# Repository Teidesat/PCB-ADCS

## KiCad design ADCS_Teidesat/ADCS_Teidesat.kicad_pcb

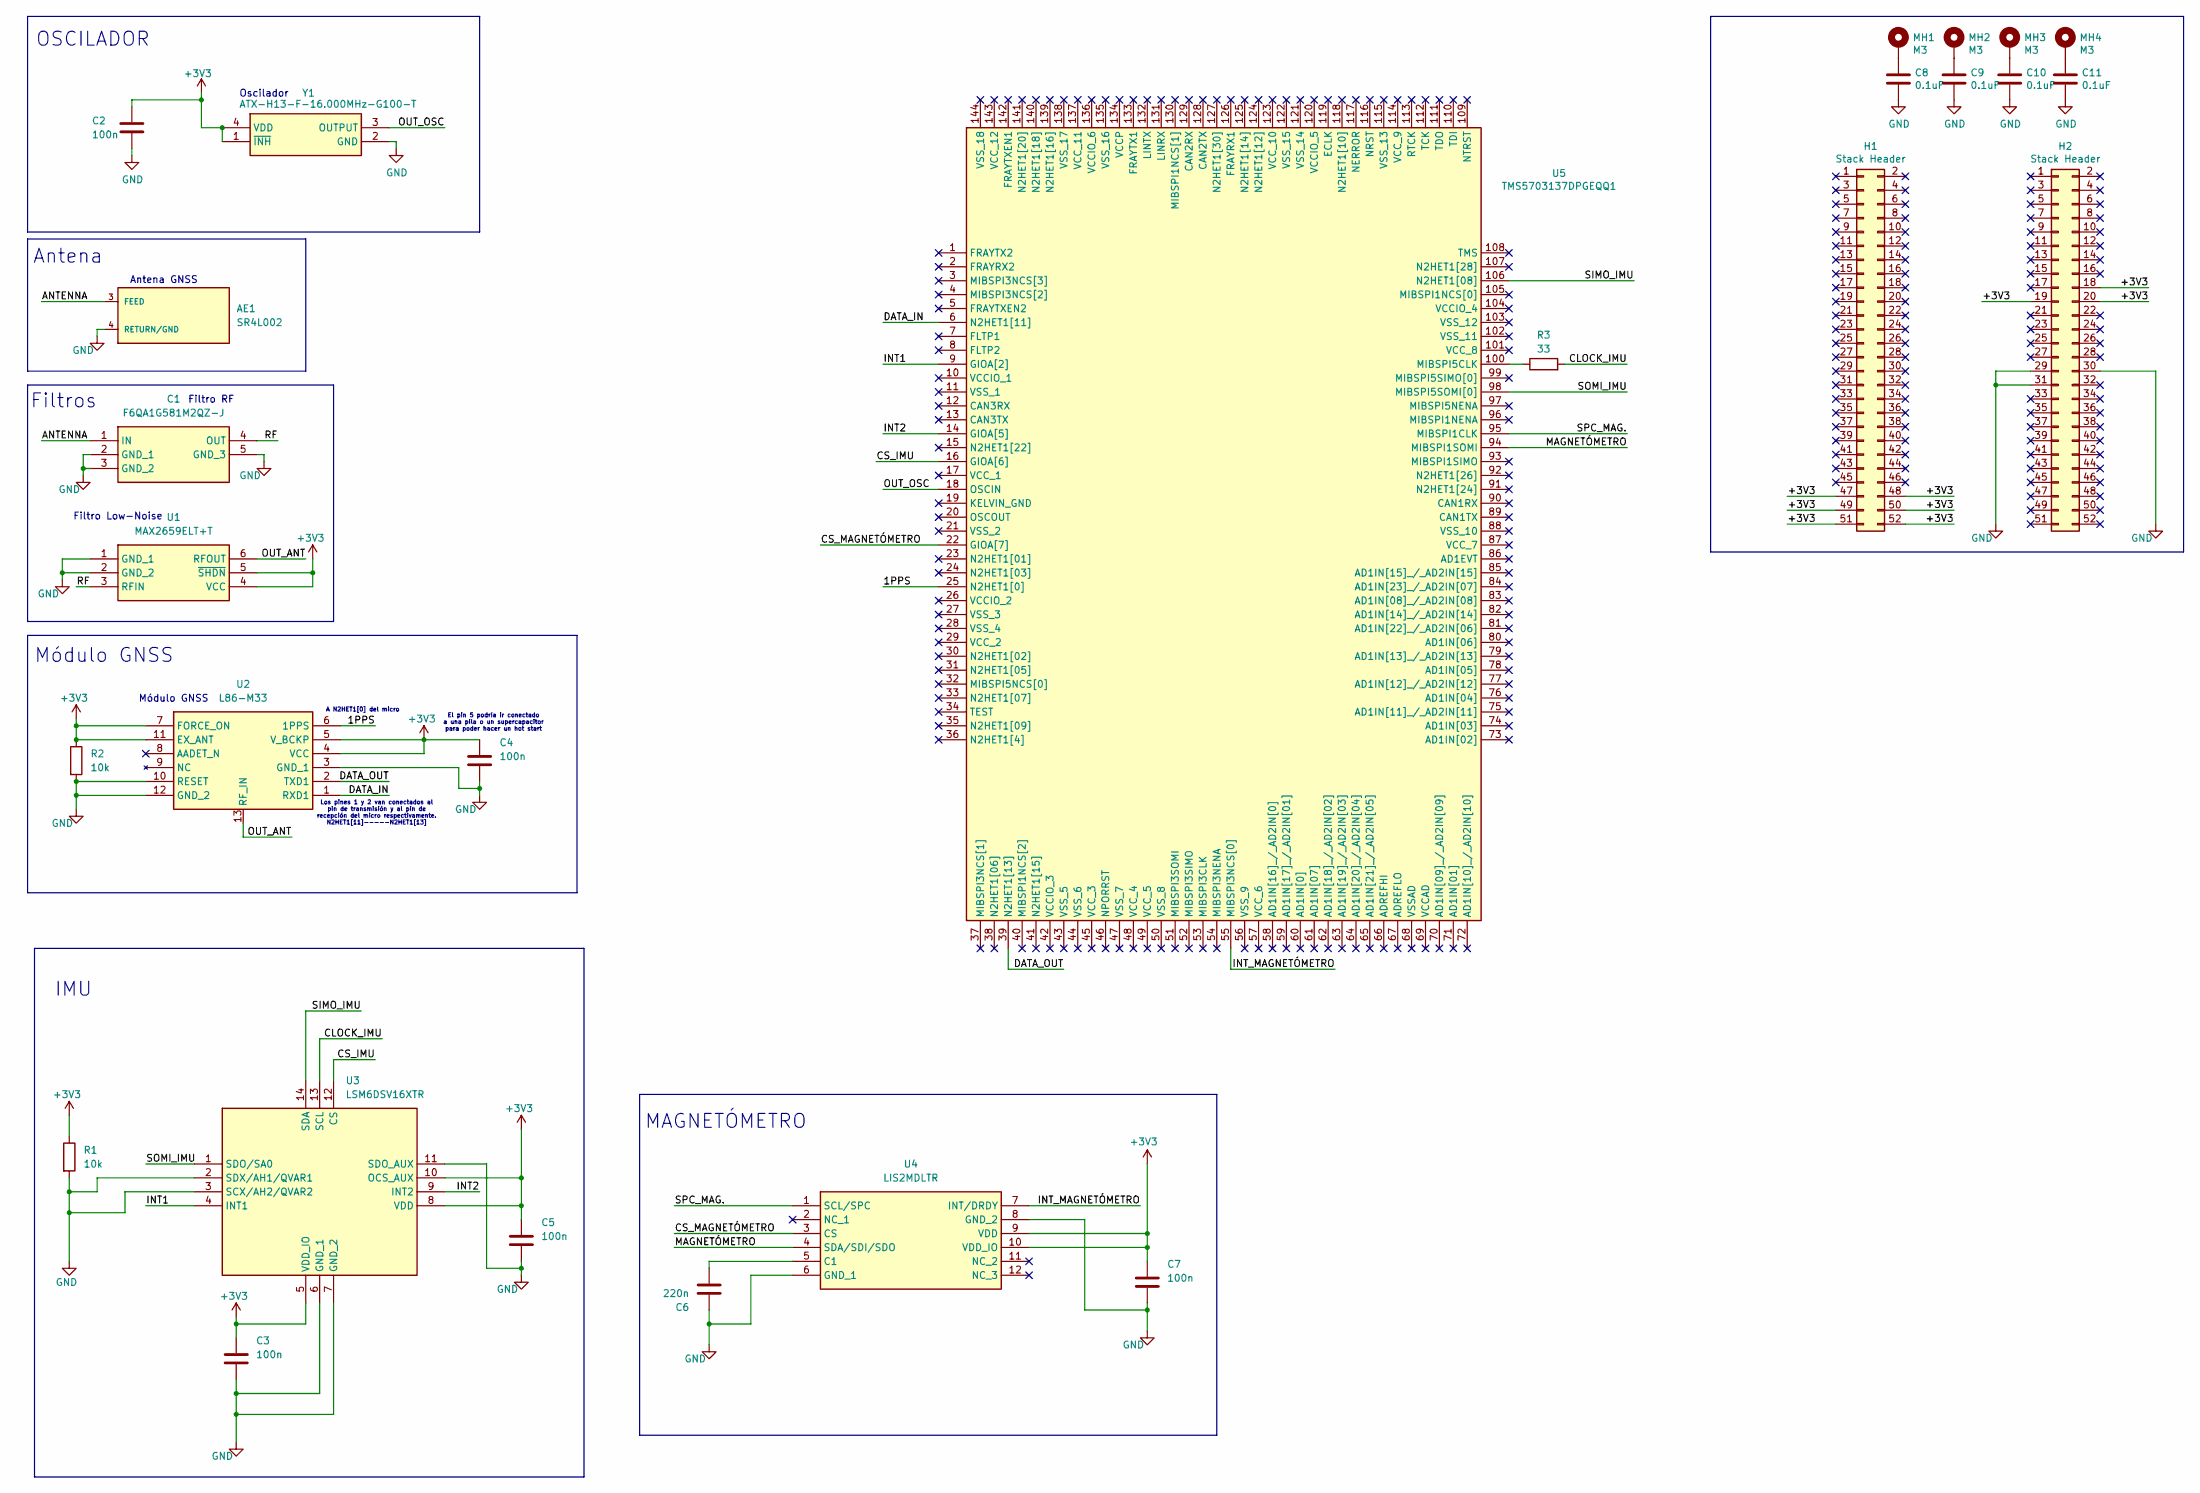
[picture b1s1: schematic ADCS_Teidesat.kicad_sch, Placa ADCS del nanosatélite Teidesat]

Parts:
AE1: SR4L002; XCVR_SR4L002
C1: F6QA1G581M2QZ-J; F6QA1G581M2QZJ; Mouser Part Number 963-F6QA1G581M2QZ-J
C2, C3, C4, C5, C7: 100n; C_0805_2012Metric
C6: 220n; C_0805_2012Metric
C8, C9, C10, C11: 0.1uF; C_0805_2012Metric
H1, H2: Stack Header; PinHeader_2x26_P2.54mm_Vertical
MH1, MH2, MH3, MH4: M3; MountingHole_3.2mm_M3_Pad
R1, R2: 10k; R_0201_0603Metric
R3: 33; R_0201_0603Metric
U1: MAX2659ELT+T; MAX2659ELTT; Mouser Part Number 700-MAX2659ELT+T
U2: L86-M33; Prueba_MODULOGNSS; Mouser Part Number 277-L86-M33
U3: LSM6DSV16XTR; XDCR_LSM6DSV16XTR; Mouser Part Number 511-LSM6DSV16XTR
U4: LIS2MDLTR; PQFN50P200X200X70-12N; Mouser Part Number 511-LIS2MDLTR
U5: TMS5703137DPGEQQ1; QFP50P2200X2200X160-144N; Manufacturer_Part_Number TMS5703137DPGEQQ1; Mouser Part Number 595-MS5703137DPGEQQ1
Y1: ATX-H13-F-16.000MHz-G100-T; ATXH13F16000MHzG100T; Mouser Part Number 815-ATXH13F1600G100T

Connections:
+3V3: C2.1, C3.1, C4.1, C5.1, C7.1, H1.47, H1.48, H1.49, H1.50, H1.51, H1.52, H2.18, H2.19, H2.20, R1.1, R2.1, U1.4 (VCC), U1.5 (~SHDN), U2.4 (VCC), U2.5 (V_BCKP), U2.7 (FORCE_ON), U2.11 (EX_ANT), U3.5 (VDD_IO), U3.8 (VDD), U3.10 (OCS_AUX), U4.9 (VDD), U4.10 (VDD_IO), Y1.1 (~INH), Y1.4 (VDD)
/1PPS: U2.6 (1PPS), U5.25 (N2HET1[0])
/ANTENNA: AE1.3 (FEED), C1.1 (IN)
/CLOCK_IMU: R3.2, U3.13 (SCL)
/CS_IMU: U3.12 (CS), U5.16 (GIOA[6])
/CS_MAGNETÓMETRO: U4.3 (CS), U5.22 (GIOA[7])
/DATA_IN: U2.1 (RXD1), U5.6 (N2HET1[11])
/DATA_OUT: U2.2 (TXD1), U5.39 (N2HET1[13])
/INT1: U3.4 (INT1), U5.9 (GIOA[2])
/INT2: U3.9 (INT2), U5.14 (GIOA[5])
/INT_MAGNETÓMETRO: U4.7 (INT/DRDY), U5.55 (MIBSPI3NCS[0])
/MAGNETÓMETRO: U4.4 (SDA/SDI/SDO), U5.94 (MIBSPI1SOMI)
/OUT_ANT: U1.6 (RFOUT), U2.13 (RF_IN)
/OUT_OSC: U5.18 (OSCIN), Y1.3 (OUTPUT)
/RF: C1.4 (OUT), U1.3 (RFIN)
/SIMO_IMU: U3.14 (SDA), U5.106 (N2HET1[08])
/SOMI_IMU: U3.1 (SDO/SA0), U5.98 (MIBSPI5SOMI[0])
/SPC_MAG.: U4.1 (SCL/SPC), U5.95 (MIBSPI1CLK)
GND: AE1.4 (RETURN/GND), C1.2 (GND_1), C1.3 (GND_2), C1.5 (GND_3), C2.2, C3.2, C4.2, C5.2, C6.1, C7.2, C8.2, C9.2, C10.2, C11.2, H2.29, H2.30, H2.31, R1.2, R2.2, U1.1 (GND_1), U1.2 (GND_2), U2.3 (GND_1), U2.10 (RESET), U2.12 (GND_2), U3.2 (SDX/AH1/QVAR1), U3.3 (SCX/AH2/QVAR2), U3.6 (GND_1), U3.7 (GND_2), U3.11 (SDO_AUX), U4.6 (GND_1), U4.8 (GND_2), Y1.2 (GND)
unnamed: C8.1, MH1.1
unnamed: C9.1, MH2.1
unnamed: C10.1, MH3.1
unnamed: C11.1, MH4.1
unnamed: C6.2, U4.5 (C1)
unnamed: R3.1, U5.100 (MIBSPI5CLK)

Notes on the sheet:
Antena GNSS
Módulo GNSS
Antena
IMU
OSCILADOR
Filtros
El pin 5 podría ir conectado a una pila o un supercapacitor para poder hacer un hot start
MAGNETÓMETRO
Filtro Low-Noise
Oscilador
A N2HET1[0] del micro
Módulo GNSS
Filtro RF
Los pines 1 y 2 van conectados al pin de transmisión y al pin de recepción del micro respectivamente. N2HET1[11]-----N2HET1[13]

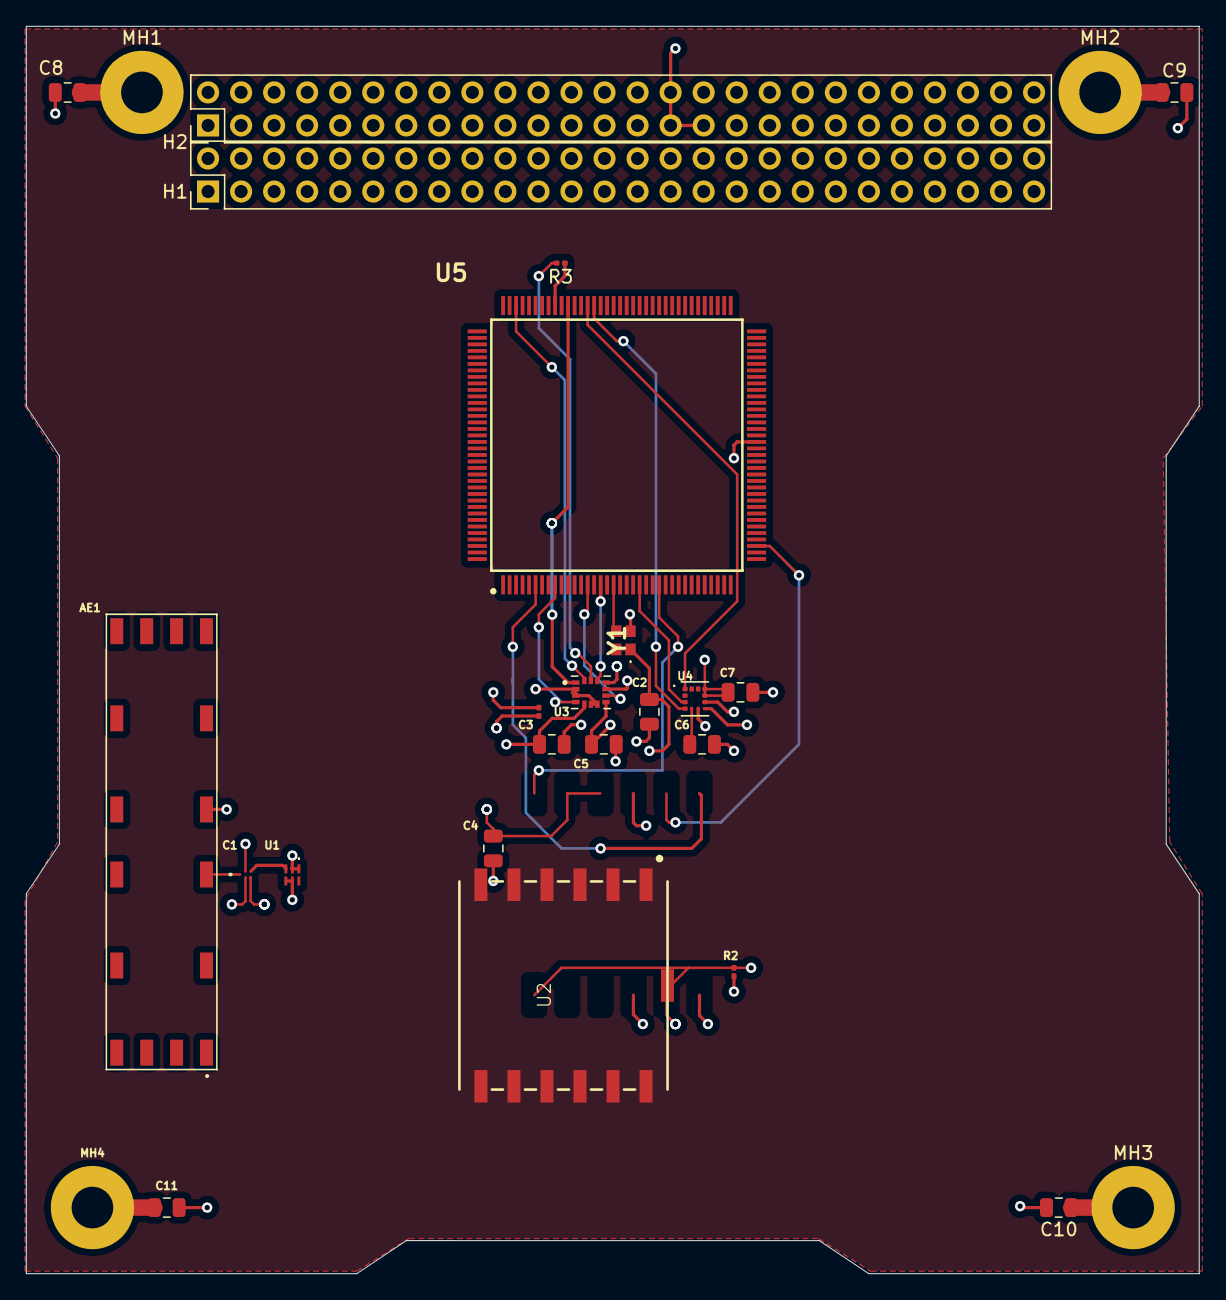
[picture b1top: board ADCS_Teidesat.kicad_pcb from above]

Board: 4 copper layers, 90.2 x 95.9 mm, 27 parts (0 on the bottom side), 25 nets.

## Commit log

2025-11-05 Esquemático ADCS
    Primer esquemático donde se han implementado los símbolos y huellas de los componentes seleccionados y se ha comenzado con el circuito de los sensores solares
2025-11-08 Desarrollo Antena, filtros y oscilador
    Circuito del oscilador, la antena GNSS y sus respectivos filtro
2025-11-09 Conexión del GNSS
2025-11-17 Arreglos de trackeo
2025-11-17 Arreglos trackeo
2025-11-17 Conexión de IMU con el Microcontrolador
    Conexión de la IMU (LSM6DSV16XTR) y del magnetómetro (LIS2MDLTR). Se han conectado de las forma que trabajen en modo SPI
2025-11-18 Gitignore
2025-11-18 Arreglo trackeo
2025-11-18 Arreglos etiquetas
    Correcciones propuestas por salvador acerca de etiquetas
2025-11-18 Trackeo
2025-11-18 Comienzo PCB
    Realizamos los últimos arreglos en las huellas de los componentes y comenzamos el diseño de la PCB
2025-11-18 Conexionado de componentes de PCB a falta de revisión
    Se ha hecho un primer enrutado de la PCB de la placa ADCS.
2025-11-19 Corrección en de los Pines 13 y 14 de la IMU
    He corregido el Pin 13 (SCL) y el Pin 14 (SDA) de la IMU según su datasheet. Además, he pasado la línea compartida entre la IMU y el magnetómetro a una única línea para este último
2025-11-21 Arreglo problemas de plantilla
    Arreglamos problemas en la plantilla y realizamos ciertas correcciones de Salvador
2025-11-21 Nuevo enrutado y correcciones de nombres y plantilla.
2025-11-21 Nuevo enrutado de PCB, corrección de nombres y de plantilla.
2025-11-23 Plano GND y Plano 3V3
    He modificado la PCB de dos capas a cuatro capas. Con esto, hemos conseguido una capa extra de GND y he añadido el plano de potencia.
2025-12-03 Mejora del enrutado y las conexiones de los componentes, además de la modificación en la distribución de los planos
    Optimización de las conexiones, liberando la capa TOP relazándolas en la capa BOTTON. Modificación de la distribución de los planos. Actualmente: TOP Layer (Plano de conexiones 1), Inner Layer 1 (GND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
2025-12-07 Últimas modificaciones de la V.0.1.
    Se han realizado las últimas modificaciones en del diseño de la PCB, se han nombrado las capas, y además, se han añadido las huellas correctas de cada componente.
2025-12-08 Modificación en la huella del módulo GNSS
    He añadido un pin que añadimos en el esquemático al símbolo del modulo GNSS, el pin 13. Hemos añadido dicho pin a la huella del componente.
